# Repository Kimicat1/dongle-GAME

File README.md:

# dongle-lighthouse
My dongle is a lighthouse. There are LEDs that recreate the light of a lighthouse. I came up with that idea because a lighthouse fits perfectly to the idea of using just LEDs for this project, I had right at the beginning. Also my little lighthouse should bring joy, like a real lighthouse only brings gives you good feelings.

## BOM (Bill of Materials)
|Item    |  Qty | Cost | Link |
|--------|------|------|------|
|WCH CH552G Microcontroller | 1 | $ 0.75 | [LCSC C111292](https://www.lcsc.com/product-detail/Microcontrollers-MCU-MPU-SOC_WCH-Jiangsu-Qin-Heng-CH552G_C111292.html)|
| Murata GRM188R72A104KA35D, 100nF, 0603 | 2 | $ 0.18 | [LCSC C77058](https://www.lcsc.com/product-detail/C77058.html) |
| 330Ω resistor, 0603 | 15 | $ 1.00 | [LCSC C4078463](https://www.lcsc.com/product-detail/C4078463.html?s_z=n_q_C4078463&globalKeyword=C4078463)
| 10kΩ resistor, 0603 | 1 | $ 0.00 | [LCSCC190610](https://www.lcsc.com/product-detail/C190610.html) |
| XUNPU TS-1088-AC02016 tactile switch | 1 | $ 0.00 | [LCSC C720475](https://www.lcsc.com/product-detail/C720475.html) |
| 0805 SMD LEDs blue | 4 | $ 1.62 | [LCSC C5879058](https://www.lcsc.com/product-detail/C5879058.html) |
| 0805 SMD LEDs white  | 11| $ 0.24 | [LCSC C130115](https://www.lcsc.com/product-detail/C130115.html?s_z=n_q_LED%2520White%25200805&spm=wm.fly.bg.12.xh&lcsc_vid=TwdaAlZXRVVbVVYDRFJcUQVVQQBcBVYCFQVdX1ICRlYxVlNeQFlYVlBRQFNYVDsOAxUeFF5JWBYZEEoKFBINSQcJGk4eFQsCAgIaSgADAwAHC0slQllZXlRTT08GEwkK) |
|PCB | 1 | $ 22.54 | [pcb-gerber.zip](https://github.com/user-attachments/files/31551457/USB_LED_DONGLE_pcb-gerber.zip.zip) 
| 3D printed case | 1 | $ 0.00 | |
| Shipping |  | $ 12.78 | |
| Total | 37 | § 39.11  | |

## screenshots
### final assembly: 
[link to Onshape](https://cad.onshape.com/documents/e6b528f845c7799f839f4ea1/w/271b4713409c857f7904aa9b/e/de40bcccf3c62f360a9d2873renderMode=0&uiState=6a90b61ebe0b5d6787ec1bef)

### PCB: 

### schematic: 

### 3D Viewer, front (first sceenshot) and back (second screenshot):

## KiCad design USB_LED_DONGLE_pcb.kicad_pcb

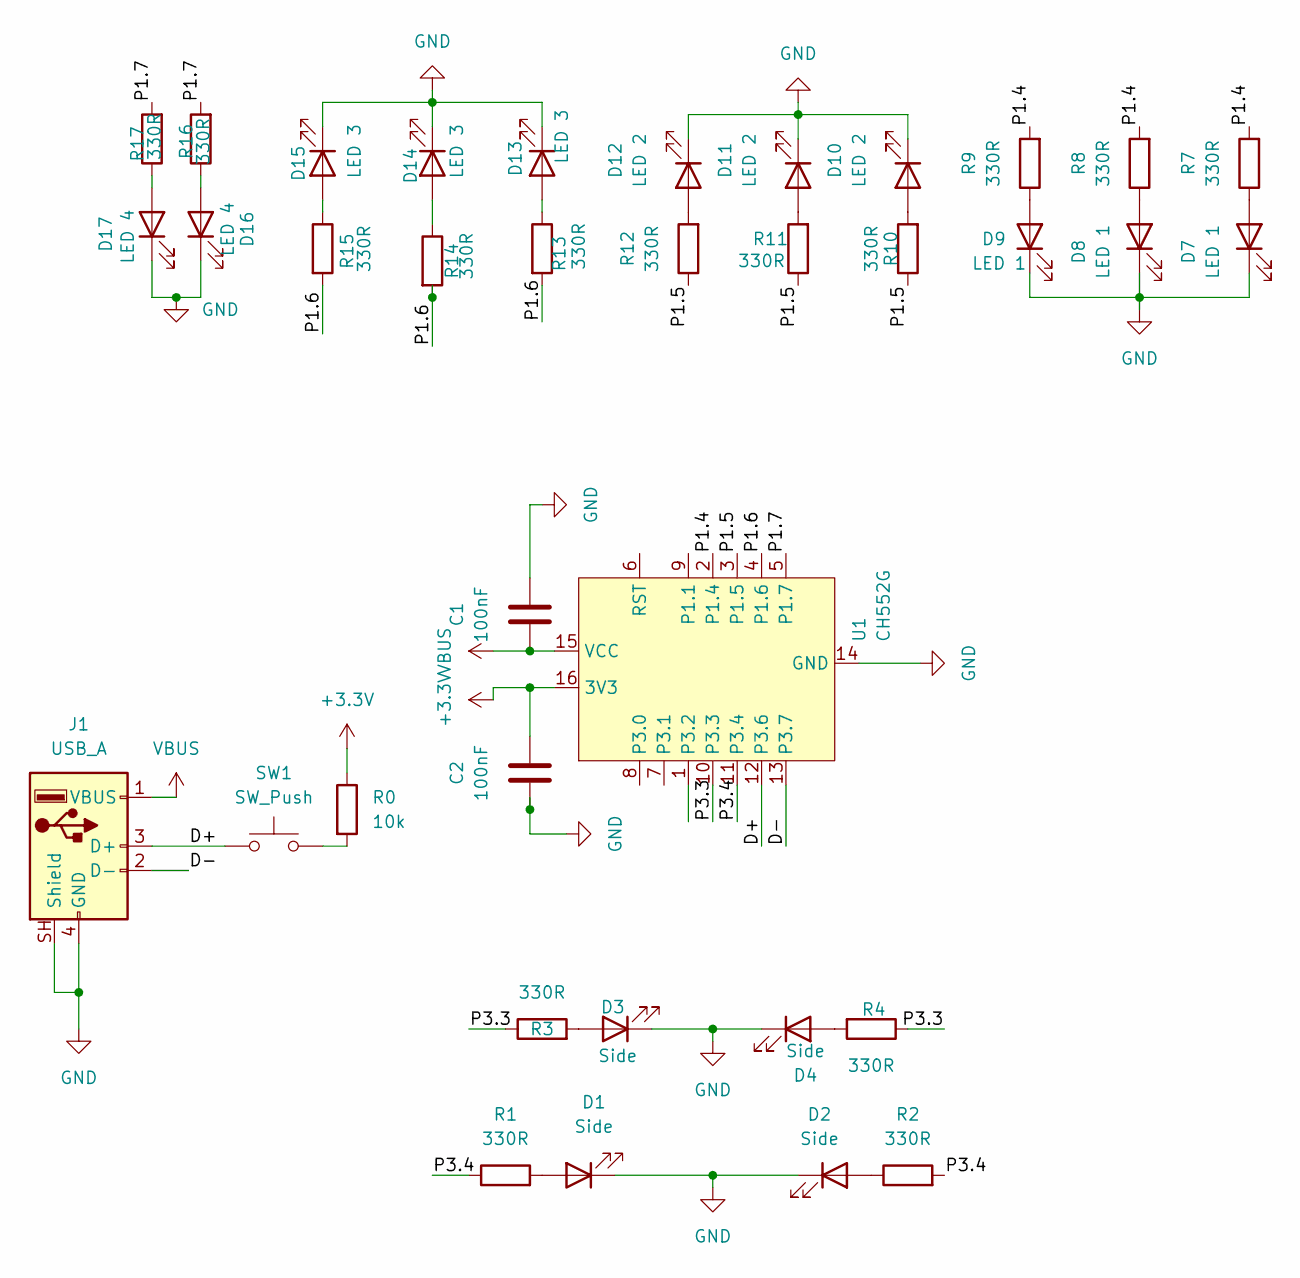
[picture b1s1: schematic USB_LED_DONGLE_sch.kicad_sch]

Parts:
C1, C2: 100nF; C_0603_1608Metric
D1, D2, D3, D4: Side; LED_0805_2012Metric
D7, D8, D9: LED 1; LED_0805_2012Metric
D10, D11, D12: LED 2; LED_0805_2012Metric
D13, D14, D15: LED 3; LED_0805_2012Metric
D16, D17: LED 4; LED_0805_2012Metric
J1: USB_A; USB-A
R0: 10k; R_0603_1608Metric
R1, R2, R3, R4, R7, R8, R9, R10, R11, R12, R13, R14, R15, R16, R17: 330R; R_0603_1608Metric
SW1: SW_Push; SW_SPST_TS-1088-xR020
U1: CH552G; SOIC-16_3.9x9.9mm_P1.27mm

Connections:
+3.3V: C2.2, R0.1, U1.16 (3V3)
/D+: J1.3 (D+), SW1.1, U1.12 (P3.6)
/D-: J1.2 (D-), U1.13 (P3.7)
/P1.4: R7.2, R8.2, R9.2, U1.2 (P1.4)
/P1.5: R10.1, R11.1, R12.1, U1.3 (P1.5)
/P1.6: R13.2, R14.2, R15.2, U1.4 (P1.6)
/P1.7: R16.2, R17.2, U1.5 (P1.7)
/P3.3: R3.1, R4.1, U1.10 (P3.3)
/P3.4: R1.1, R2.2, U1.11 (P3.4)
GND: C1.2, C2.1, D1.1 (K), D2.1 (K), D3.1 (K), D4.1 (K), D7.1 (K), D8.1 (K), D9.1 (K), D10.1 (K), D11.1 (K), D12.1 (K), D13.1 (K), D14.1 (K), D15.1 (K), D16.1 (K), D17.1 (K), J1.4 (GND), J1.SH (Shield), U1.14 (GND)
unnamed: D1.2 (A), R1.2
unnamed: D2.2 (A), R2.1
unnamed: D3.2 (A), R3.2
unnamed: D4.2 (A), R4.2
unnamed: D7.2 (A), R7.1
unnamed: D8.2 (A), R8.1
unnamed: D9.2 (A), R9.1
unnamed: D10.2 (A), R10.2
unnamed: D11.2 (A), R11.2
unnamed: D12.2 (A), R12.2
unnamed: D13.2 (A), R13.1
unnamed: D14.2 (A), R14.1
unnamed: D15.2 (A), R15.1
unnamed: D16.2 (A), R16.1
unnamed: D17.2 (A), R17.1
unnamed: R0.2, SW1.2
VBUS: C1.1, J1.1 (VBUS), U1.15 (VCC)

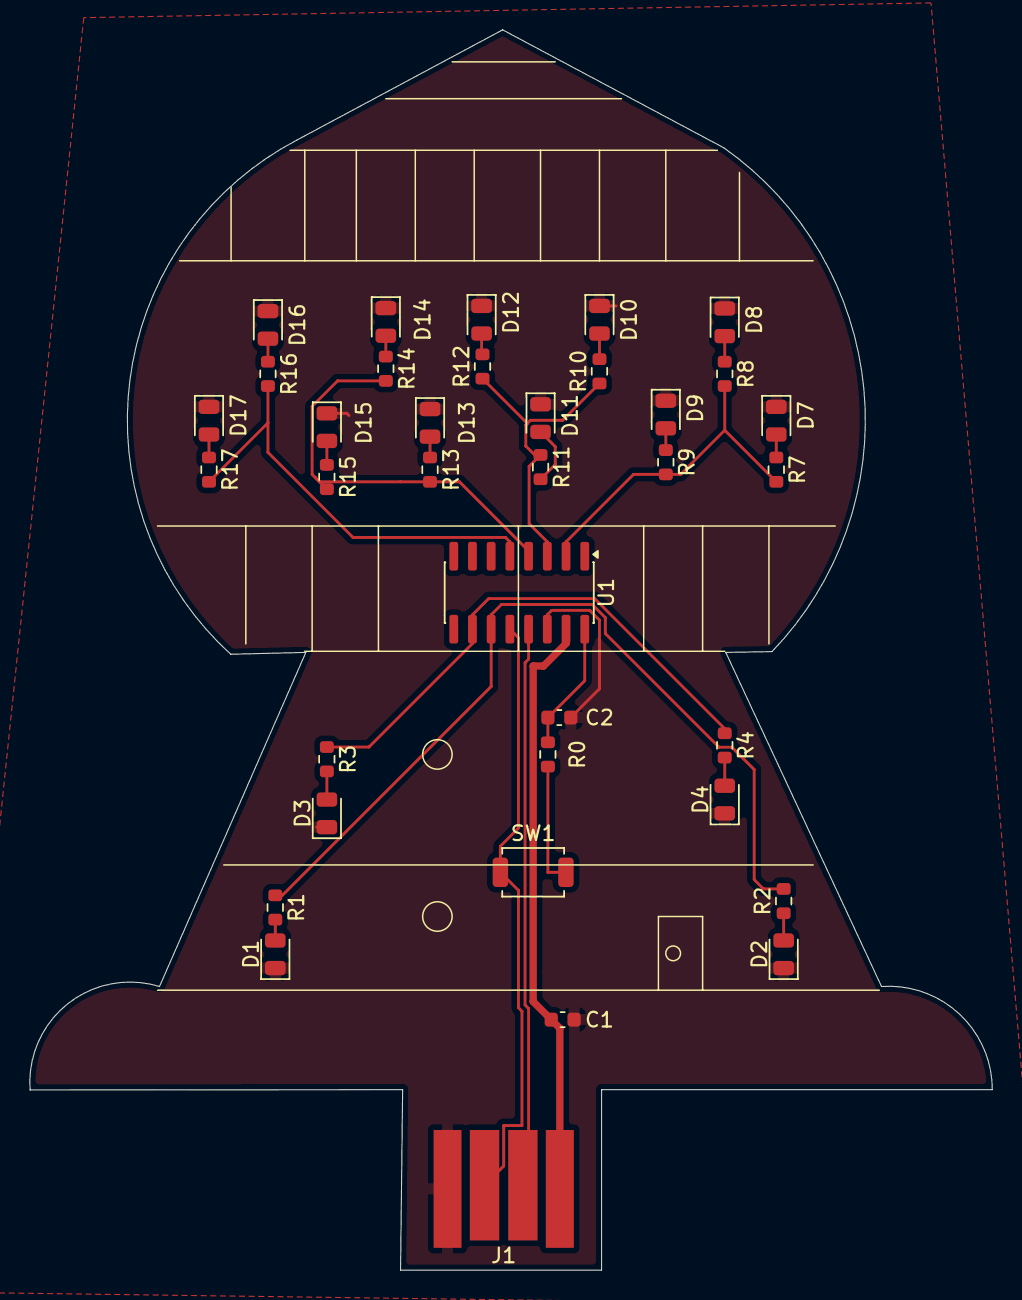
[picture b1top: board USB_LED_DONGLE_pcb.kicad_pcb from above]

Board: 2 copper layers, 65.3 x 84.2 mm, 36 parts (0 on the bottom side), 27 nets.
